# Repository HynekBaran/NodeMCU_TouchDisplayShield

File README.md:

# NodeMCU_TouchDisplayShield

Header to connect SPI ILI9341+XPT2046 touch display to NodeMCU (ESP8266), as described [here](http://nailbuster.com/?page_id=341).

Stackable long legs female header is needed to connect the display, which is on the top of NodeMCU (which one side is connected to the PCB and the other side is free):

```
|P|======-|
|C|       |
|B|==-|   |D
      |M  |i
      |C  |s
      |U  |p
     -|   |l
          |a
          |y
          |
          |   
``` 

PCB is available here:

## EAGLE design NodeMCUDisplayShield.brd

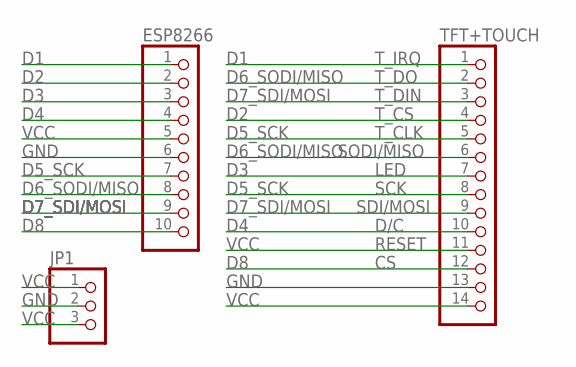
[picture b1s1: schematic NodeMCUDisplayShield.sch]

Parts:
ESP8266: PINHD-1X10/OCT; 1X10/OCT
JP1: PINHD-1X3/OCT; 1X03/OCT
TFT+TOUCH: PINHD-1X14/OCT; 1X14/OCT

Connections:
D1: ESP8266.1, TFT+TOUCH.1
D2: ESP8266.2, TFT+TOUCH.4
D3: ESP8266.3, TFT+TOUCH.7
D4: ESP8266.4, TFT+TOUCH.10
D5_SCK: ESP8266.7, TFT+TOUCH.5, TFT+TOUCH.8
D6_SODI/MISO: ESP8266.8, TFT+TOUCH.2, TFT+TOUCH.6
D7_SDI/MOSI: ESP8266.9, TFT+TOUCH.3, TFT+TOUCH.9
D8: ESP8266.10, TFT+TOUCH.12
GND: ESP8266.6, JP1.2, TFT+TOUCH.13
VCC: ESP8266.5, JP1.1, JP1.3, TFT+TOUCH.11, TFT+TOUCH.14

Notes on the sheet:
T_CLK
T_DO
T_DIN
SCK
SDI/MOSI
RESET
SODI/MISO
T_IRQ
T_CS
LED
D/C

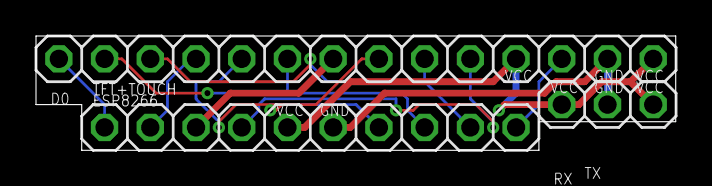
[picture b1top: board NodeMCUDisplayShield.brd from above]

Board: 2 copper layers, 35.5 x 6.3 mm, 3 parts (0 on the bottom side), 10 nets.

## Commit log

2017-03-22 Testing version candidate 1 (to be double-checked before sending to OSH)
2017-03-22 Lehce upraven potisk, pdf.
2017-03-22 .gitignore #b? #s?
2017-08-22 Single-sided version
2017-09-01 https://pcbs.io/share/zd3qw SIngle-sided.
2017-09-01 README.md update (PCB available https://pcbs.io/share/zd3qw)
2017-09-01 README.md: simple ascii graphics connection hint & pcbs.io icon
2017-09-01 pdf updated, short info in schema added
